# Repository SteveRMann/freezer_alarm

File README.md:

# freezer_alarm
---

- Board: Lolin(Wemos) D1 R2 & Mini
<br>
A DS18B20 will be inside the freezer and the Wemos D1 Mini with the OLED shield will be outside.
Temperatures are also published on MQTT:
  fahrenheightTopic= freezer/temp/f<br>
  centigradeTopic= freezer/temp/c

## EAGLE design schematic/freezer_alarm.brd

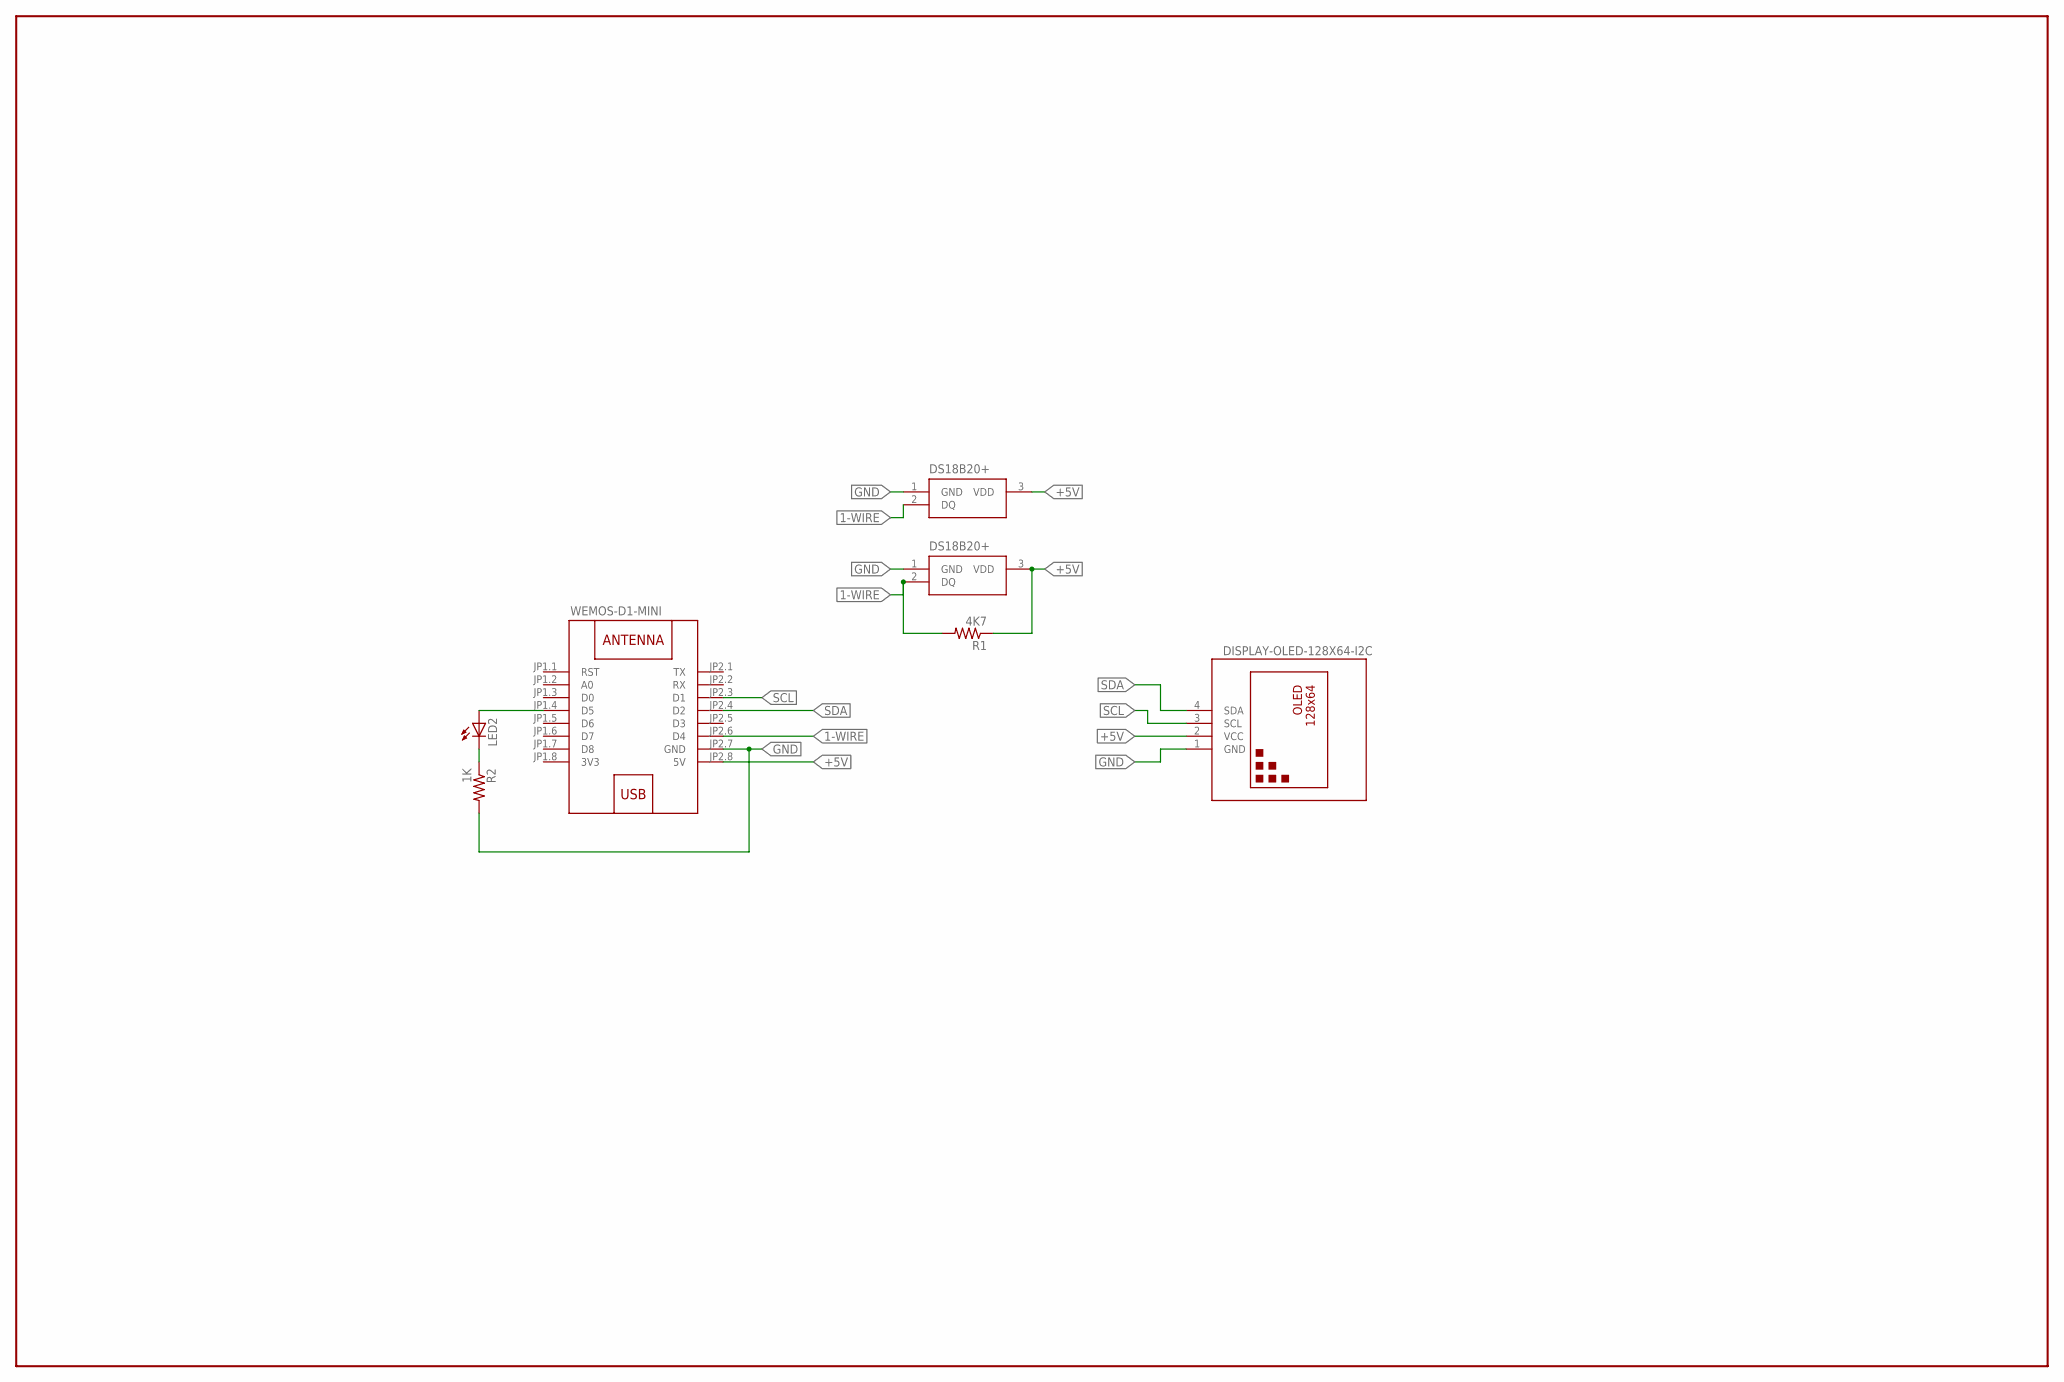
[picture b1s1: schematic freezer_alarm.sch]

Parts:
DISP: DISPLAY-OLED-128X64-I2C
IC1, IC2: DS18B20+; TO-92
LED2: LED5MM
R1: 4K7; 0207/10
R2: 1K; 0207/10
W1: WEMOS-D1-MINI

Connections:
1-WIRE: IC1.2 (DQ), IC2.2 (DQ), R1.2, W1.JP2.6 (D4)
3V3: W1.JP1.8 (3V3)
+5V: DISP.2 (VCC), IC1.3 (VDD), IC2.3 (VDD), R1.1, W1.JP2.8 (5V)
GND: DISP.1 (GND), IC1.1 (GND), IC2.1 (GND), R2.2, W1.JP2.7 (GND)
unnamed: LED2.A, W1.JP1.4 (D5)
unnamed: LED2.K (C), R2.1
SCL: DISP.3 (SCL), W1.JP2.3 (D1)
SDA: DISP.4 (SDA), W1.JP2.4 (D2)

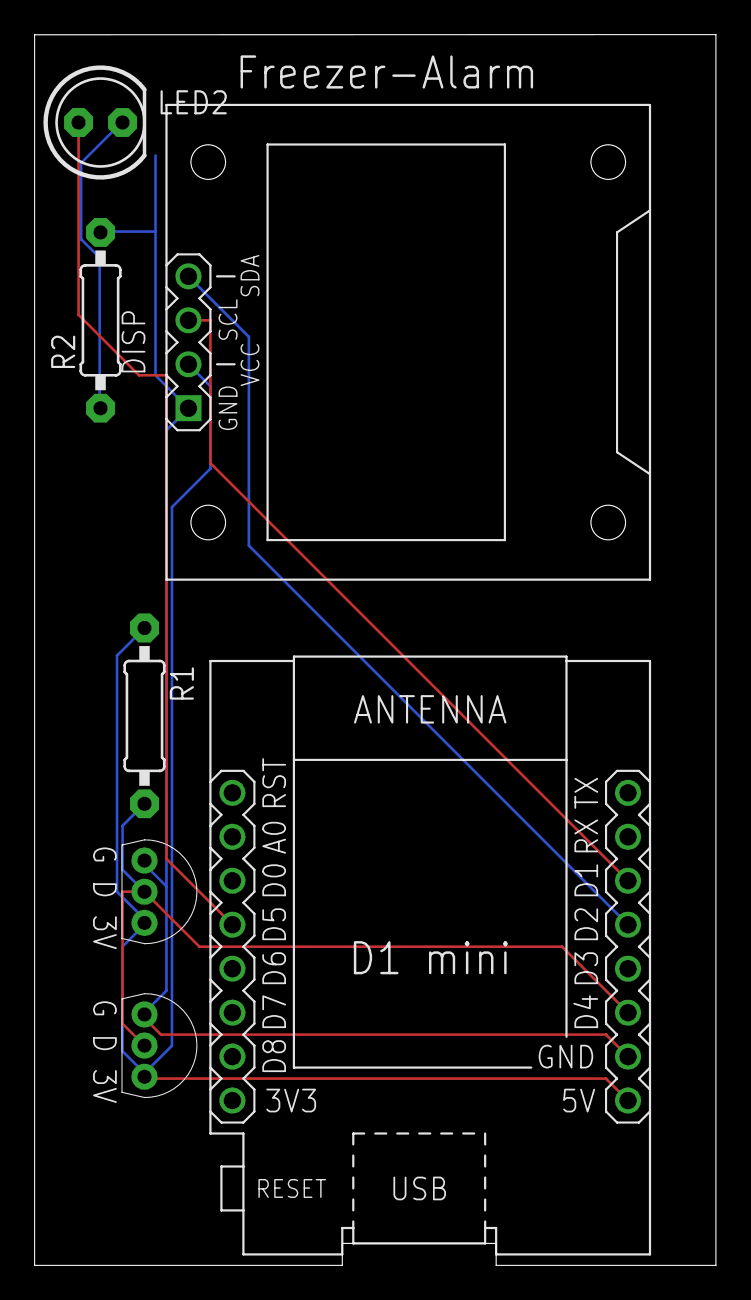
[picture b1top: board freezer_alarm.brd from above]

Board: 2 copper layers, 39.4 x 71.1 mm, 7 parts (0 on the bottom side), 7 nets.

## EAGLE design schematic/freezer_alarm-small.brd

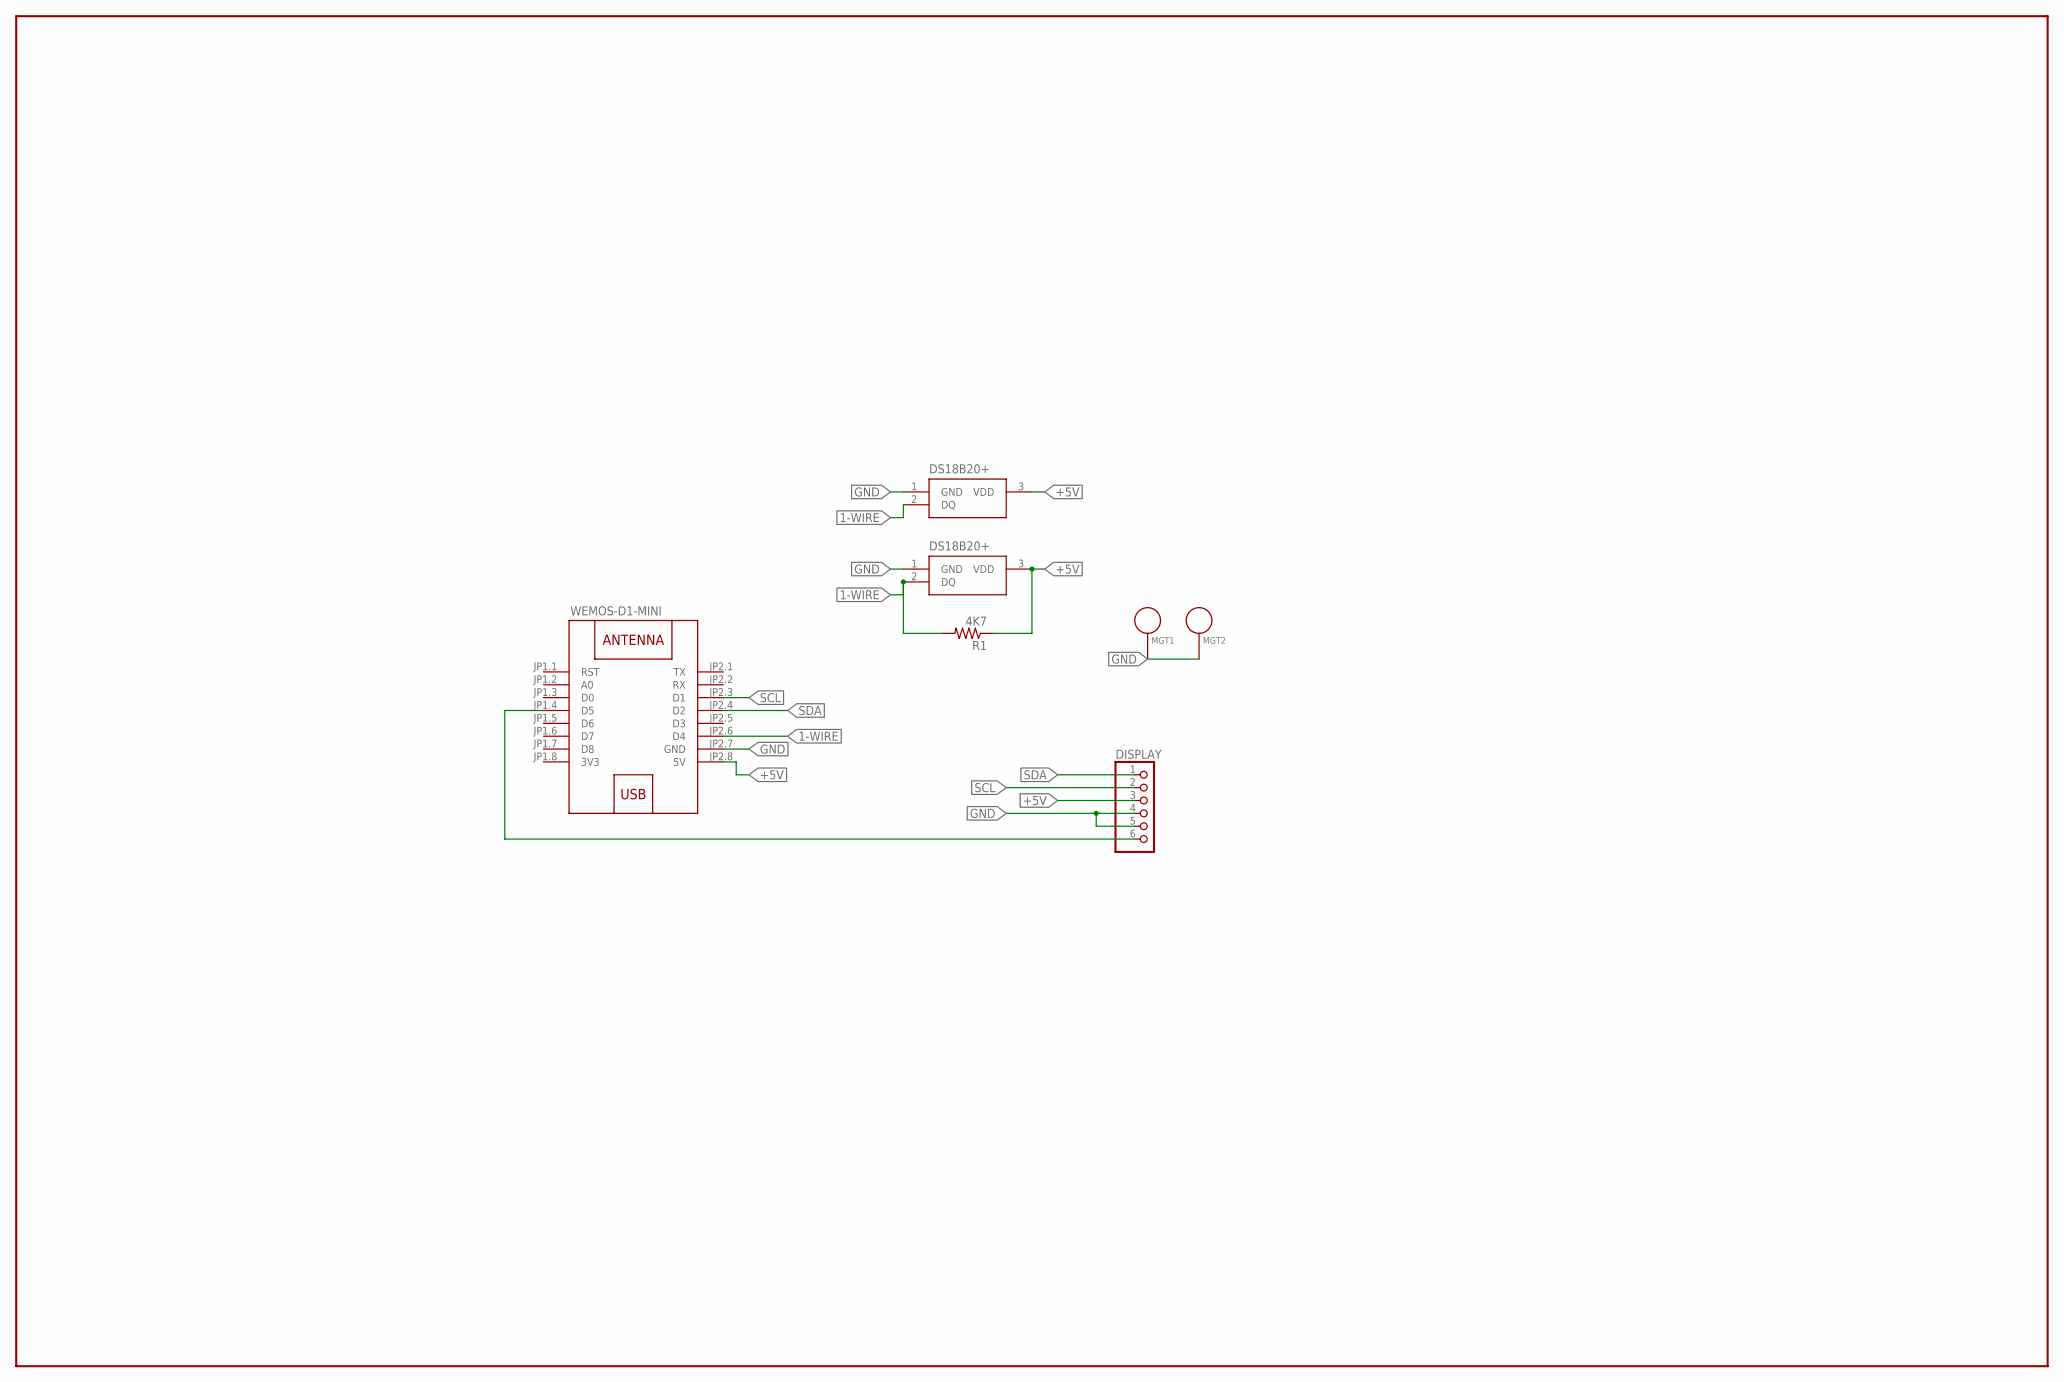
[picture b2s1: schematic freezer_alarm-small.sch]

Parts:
DISPLAY: PINHD-1X6; 1X06
IC1, IC2: DS18B20+; TO-92
MGT1, MGT2: BEAGLEBONEBLACK_MOUNTING_HOLE
R1: 4K7; 0207/10
W1: WEMOS-D1-MINI

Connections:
1-WIRE: IC1.2 (DQ), IC2.2 (DQ), R1.2, W1.JP2.6 (D4)
3V3: W1.JP1.8 (3V3)
+5V: DISPLAY.3, IC1.3 (VDD), IC2.3 (VDD), R1.1, W1.JP2.8 (5V)
GND: DISPLAY.4, DISPLAY.5, IC1.1 (GND), IC2.1 (GND), W1.JP2.7 (GND)
unnamed: MGT1.P$1, MGT2.P$1
unnamed: DISPLAY.6, W1.JP1.4 (D5)
SCL: DISPLAY.2, W1.JP2.3 (D1)
SDA: DISPLAY.1, W1.JP2.4 (D2)

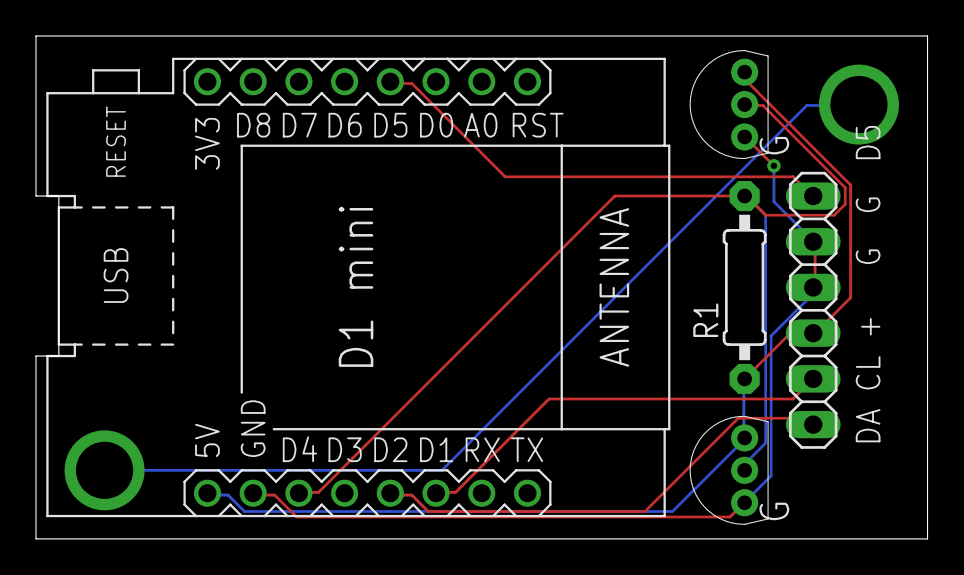
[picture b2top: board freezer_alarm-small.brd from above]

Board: 2 copper layers, 49.5 x 27.9 mm, 7 parts (0 on the bottom side), 7 nets.

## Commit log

2020-11-18 V2 working copy
2020-11-18 V2.1
    V2.1 - Added OTA
    V2.1 - Added Ticker to flash red LED if the temperature rises above the alarmSetPoint
2020-11-19 V2.2 - Added alarm set topic
2020-11-19 STL files for the case
2022-03-19 Added notch for usb plug
2022-03-19 Create placeholder
2022-03-19 Moved from main folder to src
2022-03-19 Moved arrduino files to src
2022-04-05 Added wifiMulti
2023-05-21 Added R2
    Added R2
2023-12-13 Added MAC address to publish
2023-12-13 Publish the MAC address
2023-12-13 change IOT_SSID to MY_SSID

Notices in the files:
parts and their libraries:
diy-modules: Released under the Creative Commons Attribution 4.0 International License: http://creativecommons.org/licenses/by/4.0
